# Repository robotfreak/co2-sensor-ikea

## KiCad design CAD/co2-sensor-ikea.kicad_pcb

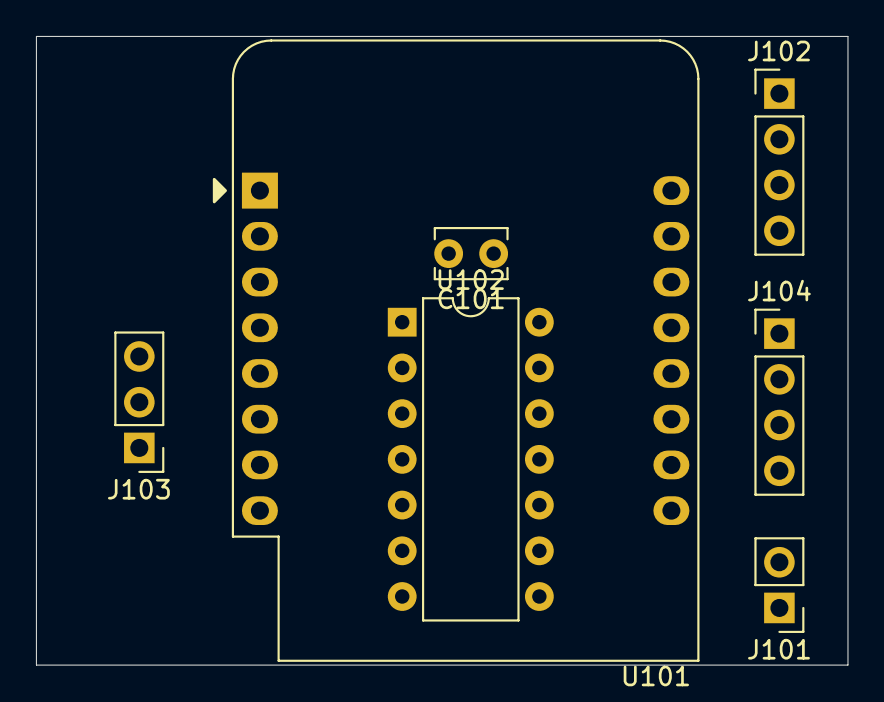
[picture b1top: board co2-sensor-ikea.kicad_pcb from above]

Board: 2 copper layers, 45.1 x 34.9 mm, 7 parts (0 on the bottom side), 16 nets, no tracks yet.

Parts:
C101: C; C_Disc_D3.8mm_W2.6mm_P2.50mm
J101: Conn_Power; PinHeader_1x02_P2.54mm_Vertical
J102: Conn_I2C; PinHeader_1x04_P2.54mm_Vertical
J103: Conn_LED; PinHeader_1x03_P2.54mm_Vertical
J104: Conn_UART; PinHeader_1x04_P2.54mm_Vertical
U101: WeMos_D1_mini; WEMOS_D1_mini_light
U102: 74HC04; DIP-14_W7.62mm

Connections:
+3V3: J102.1, U101.8
+5V: C101.1, J101.1, J104.1, U101.9, U102.14
GND: C101.2, J101.2, J102.2, J104.2, U101.10, U102.7
unnamed: J103.1, U102.8
unnamed: J103.2, U102.10
unnamed: J103.3, U102.12
unnamed: U101.4, U102.1
unnamed: U101.5, U102.3
unnamed: U101.6, U102.5
unnamed: U102.6, U102.9
unnamed: U102.4, U102.11
unnamed: U102.2, U102.13
RXIN: J104.4, U101.11
SCL: J102.3, U101.14
SDA: J102.4, U101.13
TXOUT: J104.3, U101.12

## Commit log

2021-09-02 initial release
